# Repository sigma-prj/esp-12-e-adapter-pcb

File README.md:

ESP-12E \ ESP-12F Adapter PCB Design
==============

This repository contains set of Gerber files and KiCad source project for ESP-12E\ESP-12F adapter PCB.
Presented PCB allows ESP-12-E\F modules to be plugged into breadboard.

Requirements and Dependencies
-----------------------------

Project is built using KiCad version 5.0.2

Typical Connection Schema
-----------------------------

In order to build and run projects on this module the following connection schema can be used:

Schema above represents the way how ESP module should be connected in order to run uploaded application.
In case of application needs to be flashed into ESP chip - the corresponding GPIO 0 pin needs to be pulled down.

License
-----------------------------

ESP-12E \ ESP-12F Adapter PCB Design by www.sigmaprj.com
```
To the extent possible under law, the person who associated CC0 with
'ESP-12E \ ESP-12F Adapter PCB Design' has waived all copyright and related or neighboring rights
to 'ESP-12E \ ESP-12F Adapter PCB Design'

You should have received a copy of the CC0 legalcode along with this
work.  If not, see <http://creativecommons.org/publicdomain/zero/1.0/>.
```

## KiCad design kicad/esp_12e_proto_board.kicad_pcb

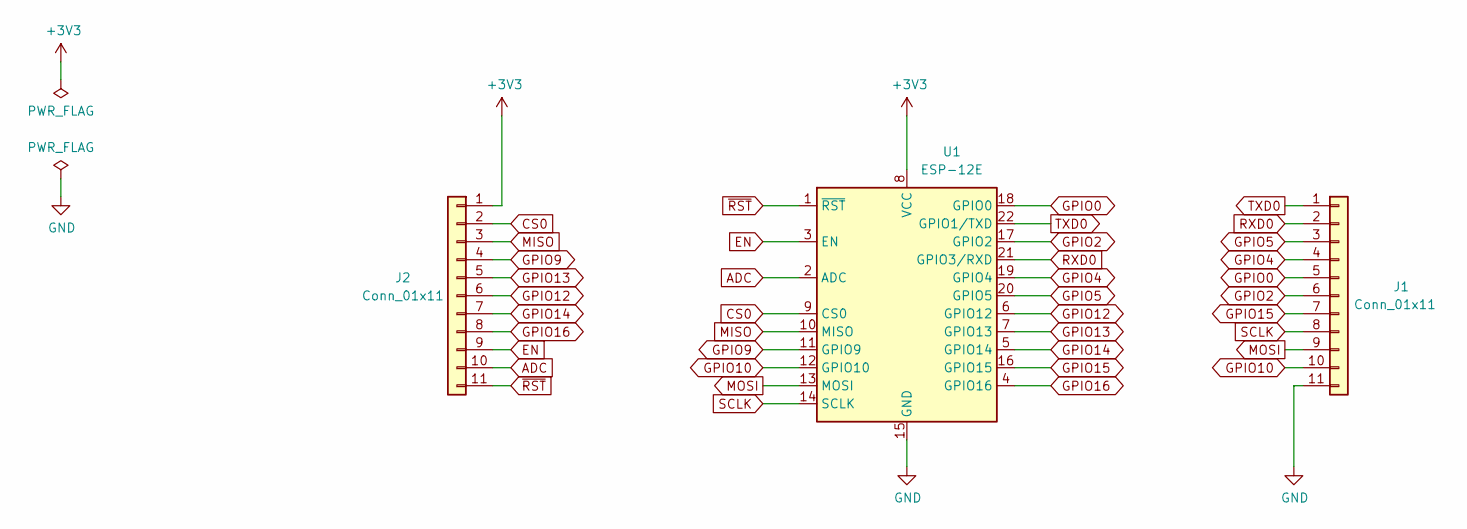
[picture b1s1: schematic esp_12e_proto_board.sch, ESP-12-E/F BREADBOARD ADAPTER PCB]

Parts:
J1, J2: Conn_01x11; PinHeader_1x11_P2.54mm_Vertical
U1: ESP-12E

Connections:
+3V3: J2.1, U1.8 (VCC)
ADC: J2.10, U1.2 (ADC)
CS0: J2.2, U1.9 (CS0)
EN: J2.9, U1.3 (EN)
GND: J1.11, U1.15 (GND)
GPIO0: J1.5, U1.18 (GPIO0)
GPIO2: J1.6, U1.17 (GPIO2)
GPIO4: J1.4, U1.19 (GPIO4)
GPIO5: J1.3, U1.20 (GPIO5)
GPIO9: J2.4, U1.11 (GPIO9)
GPIO10: J1.10, U1.12 (GPIO10)
GPIO12: J2.6, U1.6 (GPIO12)
GPIO13: J2.5, U1.7 (GPIO13)
GPIO14: J2.7, U1.5 (GPIO14)
GPIO15: J1.7, U1.16 (GPIO15)
GPIO16: J2.8, U1.4 (GPIO16)
MISO: J2.3, U1.10 (MISO)
MOSI: J1.9, U1.13 (MOSI)
RXD0: J1.2, U1.21 (GPIO3/RXD)
SCLK: J1.8, U1.14 (SCLK)
TXD0: J1.1, U1.22 (GPIO1/TXD)
~RST: J2.11, U1.1 (~RST)

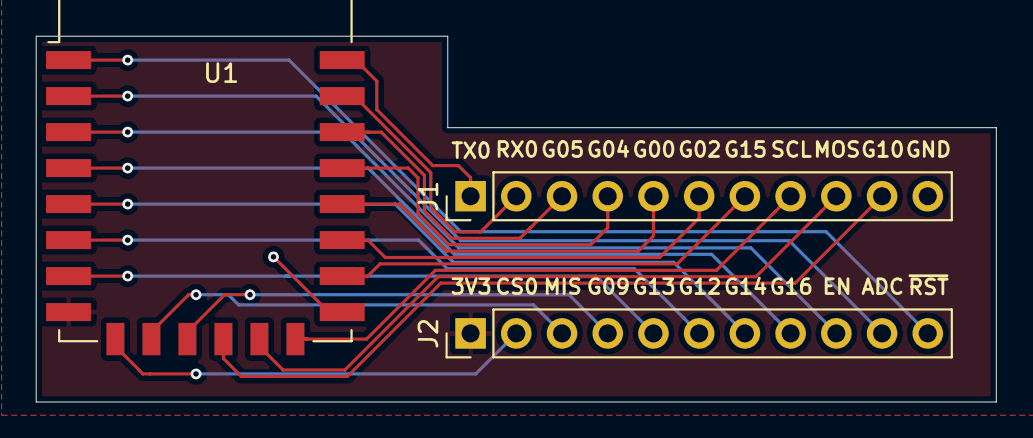
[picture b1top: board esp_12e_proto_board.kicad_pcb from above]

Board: 2 copper layers, 53.3 x 20.3 mm, 3 parts (0 on the bottom side), 22 nets.

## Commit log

2021-01-17 [ESP12E-ADAPTER-PCB] Initial PCB Design Commit, ESP Connection Schema.

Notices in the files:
kicad/esp_12e_proto_board.kicad_pcb:
License: CC0-1.0
